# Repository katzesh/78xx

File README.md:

# 78xx
78xx regulator schematic and PCB

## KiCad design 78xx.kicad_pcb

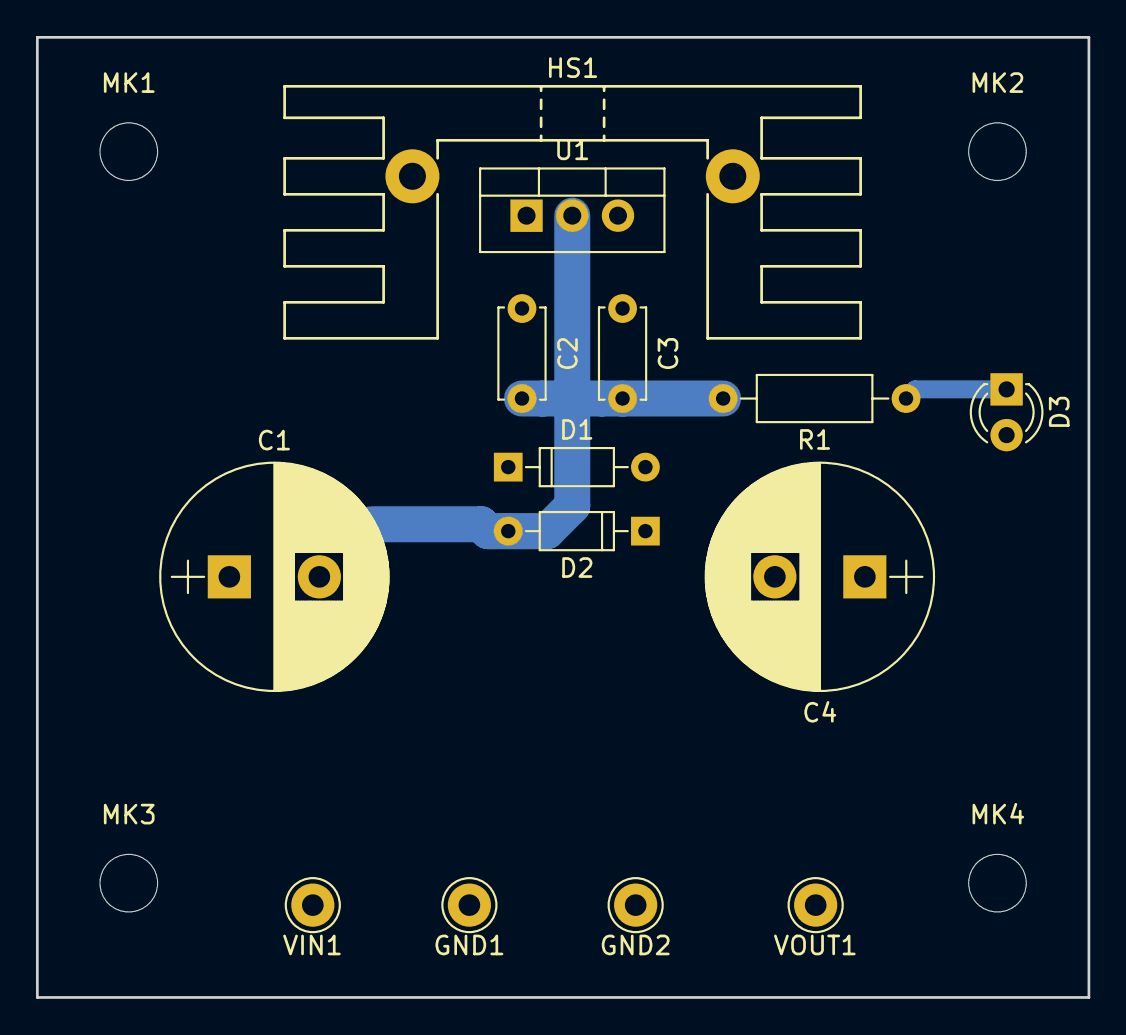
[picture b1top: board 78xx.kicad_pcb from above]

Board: 2 copper layers, 58.4 x 53.3 mm, 18 parts (0 on the bottom side), 4 nets.

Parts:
C1, C4: 100uF; CP_Radial_D12.5mm_P5.00mm
C2, C3: 0.1uF; C_Disc_D5.0mm_W2.5mm_P5.00mm
D1, D2: D; D_DO-35_SOD27_P7.62mm_Horizontal
D3: LED; LED_D3.0mm
GND1, GND2: GND; Pin_d1.0mm_L10.0mm_LooseFit
HS1: Heatsink; Heatsink_Stonecold_HS-132_32x14mm_2xFixation1.5mm
MK1, MK2: hole1; MountingHole_3.2mm_M3_DIN965
MK3: hole3; MountingHole_3.2mm_M3_DIN965
MK4: hole4; MountingHole_3.2mm_M3_DIN965
R1: 1K; R_Axial_DIN0207_L6.3mm_D2.5mm_P10.16mm_Horizontal
U1: LM7805_TO220; TO-220-3_Vertical
VIN1: 8V-; Pin_d1.0mm_L10.0mm_LooseFit
VOUT1: 5V; Pin_d1.0mm_L10.0mm_LooseFit

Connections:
/VIN: C1.1, C2.1, D1.1, U1.1, VIN1.1
/VOUT: C3.1, C4.1, D1.2, D2.1, D3.2, U1.3, VOUT1.1
GND: C1.2, C2.2, C3.2, C4.2, D2.2, GND1.1, GND2.1, R1.2, U1.2
unnamed: D3.1, R1.1
